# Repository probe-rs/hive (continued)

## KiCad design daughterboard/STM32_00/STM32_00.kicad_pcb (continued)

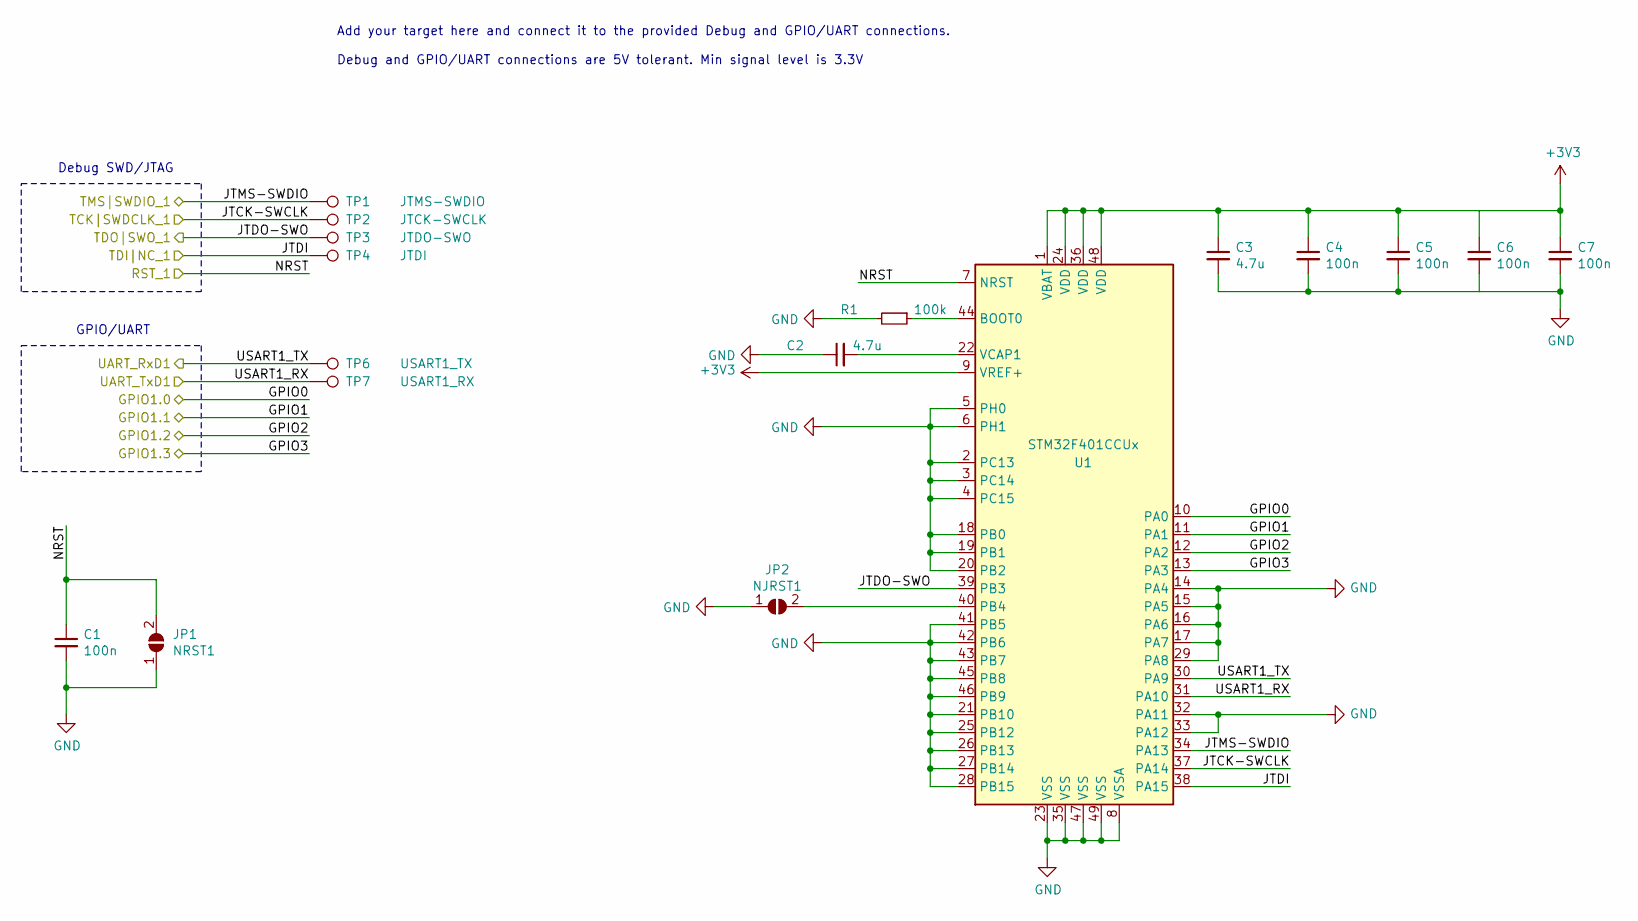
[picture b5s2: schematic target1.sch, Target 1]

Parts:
C1, C4, C5, C6, C7: 100n; C_0603_1608Metric_Pad1.05x0.95mm_HandSolder
C2, C3: 4.7u; C_0603_1608Metric_Pad1.05x0.95mm_HandSolder
JP1: NRST1; SolderJumper-2_P1.3mm_Open_TrianglePad1.0x1.5mm
JP2: NJRST1; SolderJumper-2_P1.3mm_Open_TrianglePad1.0x1.5mm
R1: 100k; R_0603_1608Metric_Pad1.05x0.95mm_HandSolder
TP1: JTMS-SWDIO; TestPoint_Pad_1.0x1.0mm
TP2: JTCK-SWCLK; TestPoint_Pad_1.0x1.0mm
TP3: JTDO-SWO; TestPoint_Pad_1.0x1.0mm
TP4: JTDI; TestPoint_Pad_1.0x1.0mm
TP6: USART1_TX; TestPoint_Pad_1.0x1.0mm
TP7: USART1_RX; TestPoint_Pad_1.0x1.0mm
U1: STM32F401CCUx; QFN-48-1EP_7x7mm_P0.5mm_EP5.6x5.6mm

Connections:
+3V3: C3.1, C4.1, C5.1, C6.1, C7.1, U1.1 (VBAT), U1.9 (VREF+), U1.24 (VDD), U1.36 (VDD), U1.48 (VDD); also elsewhere on the board
/Target 1/GPIO1.0: U1.10 (PA0); also elsewhere on the board
/Target 1/GPIO1.1: U1.11 (PA1); also elsewhere on the board
/Target 1/GPIO1.2: U1.12 (PA2); also elsewhere on the board
/Target 1/GPIO1.3: U1.13 (PA3); also elsewhere on the board
/Target 1/RST_1: C1.1, JP1.2 (B), U1.7 (NRST); also elsewhere on the board
/Target 1/TCK|SWDCLK_1: TP2.1, U1.37 (PA14); also elsewhere on the board
/Target 1/TDI|NC_1: TP4.1, U1.38 (PA15); also elsewhere on the board
/Target 1/TDO|SWO_1: TP3.1, U1.39 (PB3); also elsewhere on the board
/Target 1/TMS|SWDIO_1: TP1.1, U1.34 (PA13); also elsewhere on the board
/Target 1/UART_RxD1: TP6.1, U1.30 (PA9); also elsewhere on the board
/Target 1/UART_TxD1: TP7.1, U1.31 (PA10); also elsewhere on the board
GND: C1.2, C2.1, C3.2, C4.2, C5.2, C6.2, C7.2, JP1.1 (A), JP2.1 (A), R1.2, U1.2 (PC13), U1.3 (PC14), U1.4 (PC15), U1.5 (PH0), U1.6 (PH1), U1.8 (VSSA), U1.14 (PA4), U1.15 (PA5), U1.16 (PA6), U1.17 (PA7), U1.18 (PB0), U1.19 (PB1), U1.20 (PB2), U1.21 (PB10), U1.23 (VSS), U1.25 (PB12), U1.26 (PB13), U1.27 (PB14), U1.28 (PB15), U1.29 (PA8), U1.32 (PA11), U1.33 (PA12), U1.35 (VSS), U1.41 (PB5), U1.42 (PB6), U1.43 (PB7), U1.45 (PB8), U1.46 (PB9), U1.47 (VSS), U1.49 (VSS); also elsewhere on the board
unnamed: C2.2, U1.22 (VCAP1)
unnamed: JP2.2 (B), U1.40 (PB4)
unnamed: R1.1, U1.44 (BOOT0)

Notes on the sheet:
Debug SWD/JTAG
GPIO/UART
Add your target here and connect it to the provided Debug and GPIO/UART connections. Debug and GPIO/UART connections are 5V tolerant. Min signal level is 3.3V

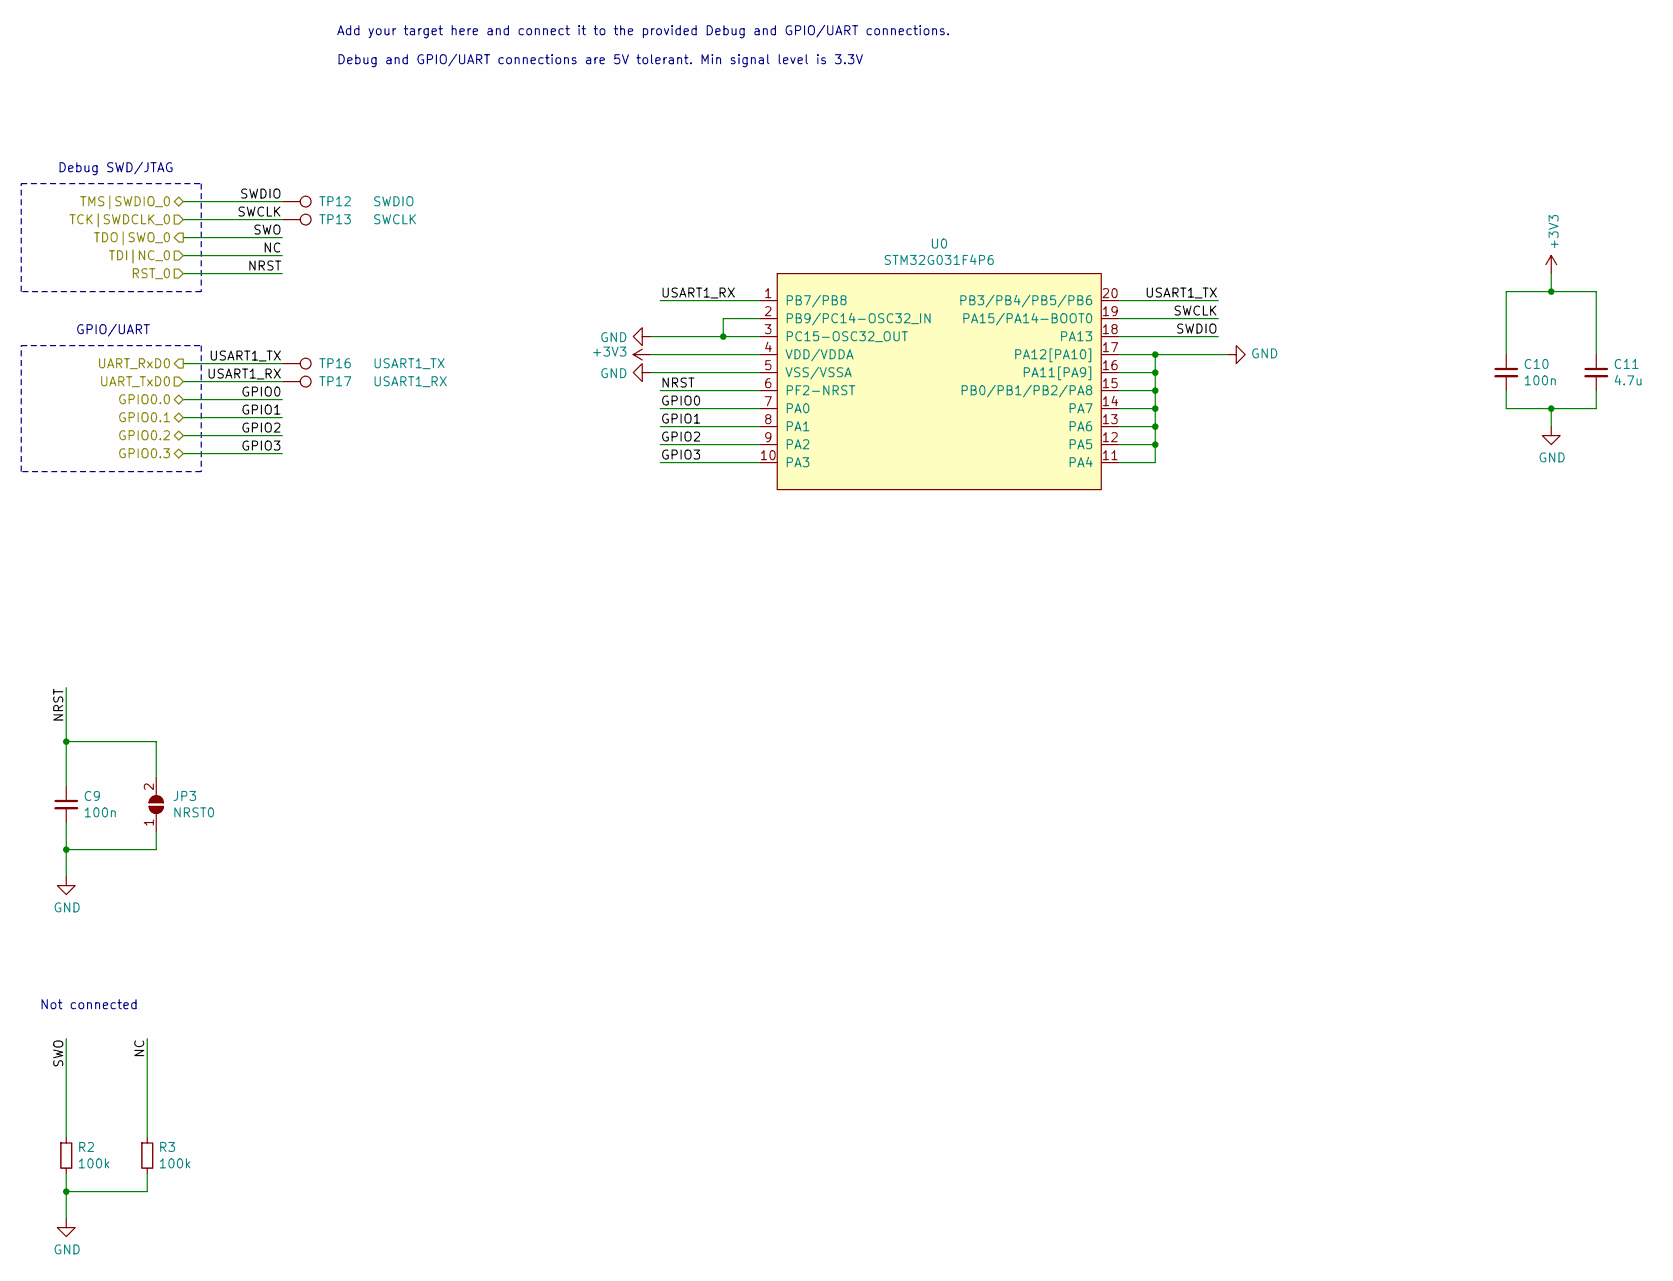
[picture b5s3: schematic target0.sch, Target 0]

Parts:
C9, C10: 100n; C_0603_1608Metric_Pad1.05x0.95mm_HandSolder
C11: 4.7u; C_0603_1608Metric_Pad1.05x0.95mm_HandSolder
JP3: NRST0; SolderJumper-2_P1.3mm_Open_TrianglePad1.0x1.5mm
R2, R3: 100k; R_0603_1608Metric_Pad1.05x0.95mm_HandSolder
TP12: SWDIO; TestPoint_Pad_1.0x1.0mm
TP13: SWCLK; TestPoint_Pad_1.0x1.0mm
TP16: USART1_TX; TestPoint_Pad_1.0x1.0mm
TP17: USART1_RX; TestPoint_Pad_1.0x1.0mm
U0: STM32G031F4P6; SOP65P640X120-20N

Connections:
+3V3: C10.1, C11.1, U0.4 (VDD/VDDA); also elsewhere on the board
/Target 0/GPIO0.0: U0.7 (PA0); also elsewhere on the board
/Target 0/GPIO0.1: U0.8 (PA1); also elsewhere on the board
/Target 0/GPIO0.2: U0.9 (PA2); also elsewhere on the board
/Target 0/GPIO0.3: U0.10 (PA3); also elsewhere on the board
/Target 0/RST_0: C9.1, JP3.2 (B), U0.6 (PF2-NRST); also elsewhere on the board
/Target 0/TCK|SWDCLK_0: TP13.1, U0.19 (PA15/PA14-BOOT0); also elsewhere on the board
/Target 0/TDI|NC_0: R3.1; also elsewhere on the board
/Target 0/TDO|SWO_0: R2.1; also elsewhere on the board
/Target 0/TMS|SWDIO_0: TP12.1, U0.18 (PA13); also elsewhere on the board
/Target 0/UART_RxD0: TP16.1, U0.20 (PB3/PB4/PB5/PB6); also elsewhere on the board
/Target 0/UART_TxD0: TP17.1, U0.1 (PB7/PB8); also elsewhere on the board
GND: C9.2, C10.2, C11.2, JP3.1 (A), R2.2, R3.2, U0.2 (PB9/PC14-OSC32_IN), U0.3 (PC15-OSC32_OUT), U0.5 (VSS/VSSA), U0.11 (PA4), U0.12 (PA5), U0.13 (PA6), U0.14 (PA7), U0.15 (PB0/PB1/PB2/PA8), U0.16 (PA11[PA9]), U0.17 (PA12[PA10]); also elsewhere on the board

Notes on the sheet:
Debug SWD/JTAG
GPIO/UART
Add your target here and connect it to the provided Debug and GPIO/UART connections. Debug and GPIO/UART connections are 5V tolerant. Min signal level is 3.3V
Not connected

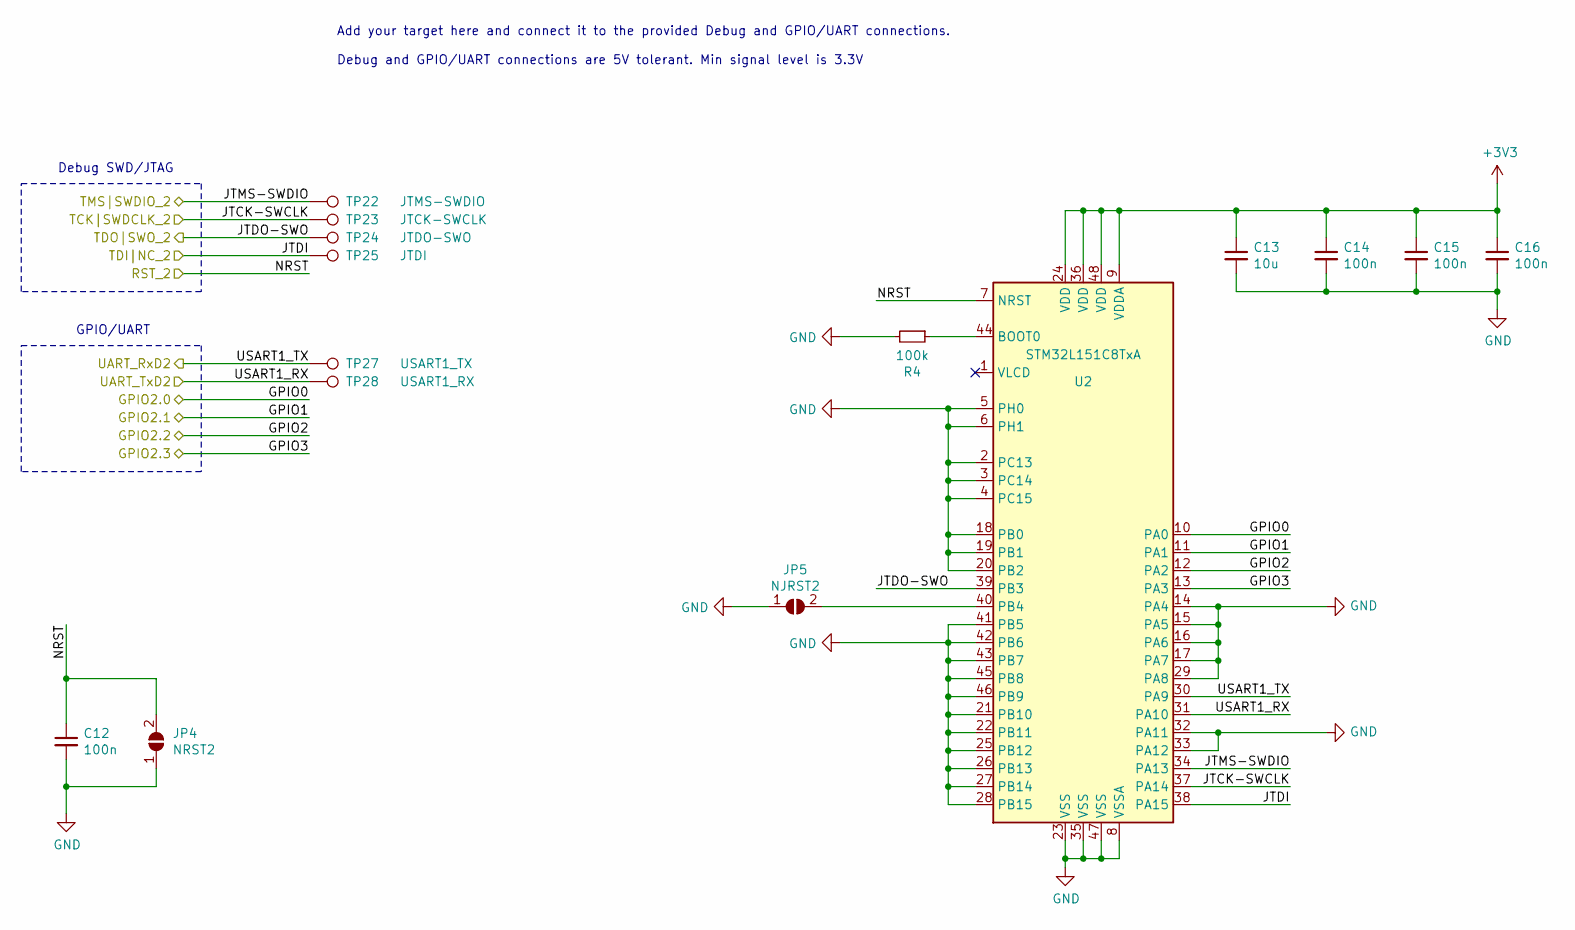
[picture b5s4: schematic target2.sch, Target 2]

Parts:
C12, C14, C15, C16: 100n; C_0603_1608Metric_Pad1.05x0.95mm_HandSolder
C13: 10u; C_0603_1608Metric_Pad1.05x0.95mm_HandSolder
JP4: NRST2; SolderJumper-2_P1.3mm_Open_TrianglePad1.0x1.5mm
JP5: NJRST2; SolderJumper-2_P1.3mm_Open_TrianglePad1.0x1.5mm
R4: 100k; R_0603_1608Metric_Pad1.05x0.95mm_HandSolder
TP22: JTMS-SWDIO; TestPoint_Pad_1.0x1.0mm
TP23: JTCK-SWCLK; TestPoint_Pad_1.0x1.0mm
TP24: JTDO-SWO; TestPoint_Pad_1.0x1.0mm
TP25: JTDI; TestPoint_Pad_1.0x1.0mm
TP27: USART1_TX; TestPoint_Pad_1.0x1.0mm
TP28: USART1_RX; TestPoint_Pad_1.0x1.0mm
U2: STM32L151C8TxA; LQFP-48_7x7mm_P0.5mm

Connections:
+3V3: C13.1, C14.1, C15.1, C16.1, U2.9 (VDDA), U2.24 (VDD), U2.36 (VDD), U2.48 (VDD); also elsewhere on the board
/Target 2/GPIO2.0: U2.10 (PA0); also elsewhere on the board
/Target 2/GPIO2.1: U2.11 (PA1); also elsewhere on the board
/Target 2/GPIO2.2: U2.12 (PA2); also elsewhere on the board
/Target 2/GPIO2.3: U2.13 (PA3); also elsewhere on the board
/Target 2/RST_2: C12.1, JP4.2 (B), U2.7 (NRST); also elsewhere on the board
/Target 2/TCK|SWDCLK_2: TP23.1, U2.37 (PA14); also elsewhere on the board
/Target 2/TDI|NC_2: TP25.1, U2.38 (PA15); also elsewhere on the board
/Target 2/TDO|SWO_2: TP24.1, U2.39 (PB3); also elsewhere on the board
/Target 2/TMS|SWDIO_2: TP22.1, U2.34 (PA13); also elsewhere on the board
/Target 2/UART_RxD2: TP27.1, U2.30 (PA9); also elsewhere on the board
/Target 2/UART_TxD2: TP28.1, U2.31 (PA10); also elsewhere on the board
GND: C12.2, C13.2, C14.2, C15.2, C16.2, JP4.1 (A), JP5.1 (A), R4.2, U2.2 (PC13), U2.3 (PC14), U2.4 (PC15), U2.5 (PH0), U2.6 (PH1), U2.8 (VSSA), U2.14 (PA4), U2.15 (PA5), U2.16 (PA6), U2.17 (PA7), U2.18 (PB0), U2.19 (PB1), U2.20 (PB2), U2.21 (PB10), U2.22 (PB11), U2.23 (VSS), U2.25 (PB12), U2.26 (PB13), U2.27 (PB14), U2.28 (PB15), U2.29 (PA8), U2.32 (PA11), U2.33 (PA12), U2.35 (VSS), U2.41 (PB5), U2.42 (PB6), U2.43 (PB7), U2.45 (PB8), U2.46 (PB9), U2.47 (VSS); also elsewhere on the board
unnamed: JP5.2 (B), U2.40 (PB4)
unnamed: R4.1, U2.44 (BOOT0)

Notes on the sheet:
Debug SWD/JTAG
GPIO/UART
Add your target here and connect it to the provided Debug and GPIO/UART connections. Debug and GPIO/UART connections are 5V tolerant. Min signal level is 3.3V

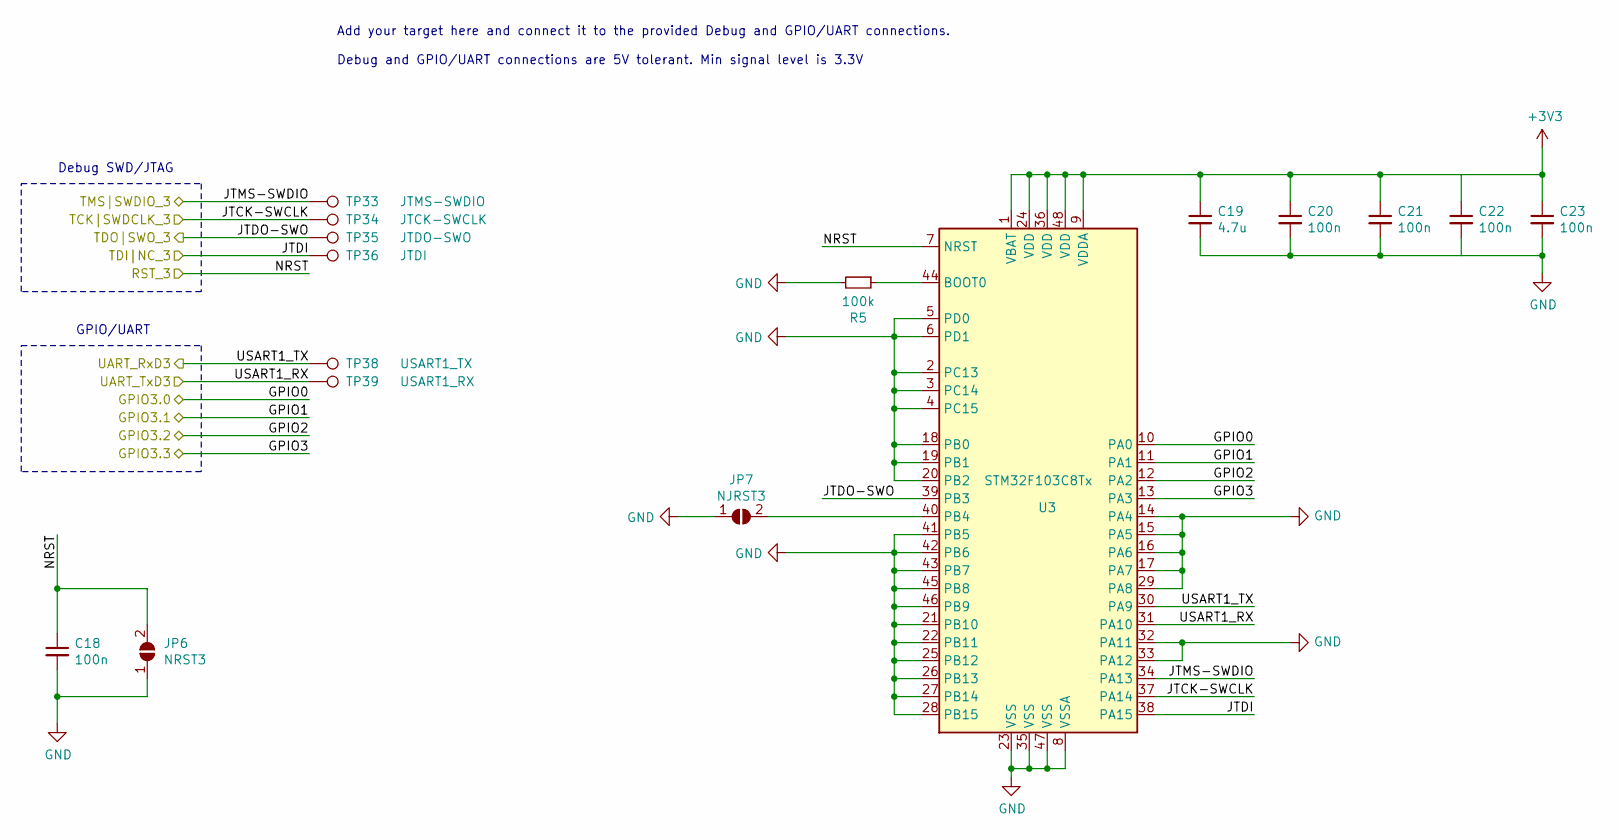
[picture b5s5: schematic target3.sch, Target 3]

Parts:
C18, C20, C21, C22, C23: 100n; C_0603_1608Metric_Pad1.05x0.95mm_HandSolder
C19: 4.7u; C_0603_1608Metric_Pad1.05x0.95mm_HandSolder
JP6: NRST3; SolderJumper-2_P1.3mm_Open_TrianglePad1.0x1.5mm
JP7: NJRST3; SolderJumper-2_P1.3mm_Open_TrianglePad1.0x1.5mm
R5: 100k; R_0603_1608Metric_Pad1.05x0.95mm_HandSolder
TP33: JTMS-SWDIO; TestPoint_Pad_1.0x1.0mm
TP34: JTCK-SWCLK; TestPoint_Pad_1.0x1.0mm
TP35: JTDO-SWO; TestPoint_Pad_1.0x1.0mm
TP36: JTDI; TestPoint_Pad_1.0x1.0mm
TP38: USART1_TX; TestPoint_Pad_1.0x1.0mm
TP39: USART1_RX; TestPoint_Pad_1.0x1.0mm
U3: STM32F103C8Tx; LQFP-48_7x7mm_P0.5mm

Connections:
+3V3: C19.1, C20.1, C21.1, C22.1, C23.1, U3.1 (VBAT), U3.9 (VDDA), U3.24 (VDD), U3.36 (VDD), U3.48 (VDD); also elsewhere on the board
/Target 3/GPIO3.0: U3.10 (PA0); also elsewhere on the board
/Target 3/GPIO3.1: U3.11 (PA1); also elsewhere on the board
/Target 3/GPIO3.2: U3.12 (PA2); also elsewhere on the board
/Target 3/GPIO3.3: U3.13 (PA3); also elsewhere on the board
/Target 3/RST_3: C18.1, JP6.2 (B), U3.7 (NRST); also elsewhere on the board
/Target 3/TCK|SWDCLK_3: TP34.1, U3.37 (PA14); also elsewhere on the board
/Target 3/TDI|NC_3: TP36.1, U3.38 (PA15); also elsewhere on the board
/Target 3/TDO|SWO_3: TP35.1, U3.39 (PB3); also elsewhere on the board
/Target 3/TMS|SWDIO_3: TP33.1, U3.34 (PA13); also elsewhere on the board
/Target 3/UART_RxD3: TP38.1, U3.30 (PA9); also elsewhere on the board
/Target 3/UART_TxD3: TP39.1, U3.31 (PA10); also elsewhere on the board
GND: C18.2, C19.2, C20.2, C21.2, C22.2, C23.2, JP6.1 (A), JP7.1 (A), R5.2, U3.2 (PC13), U3.3 (PC14), U3.4 (PC15), U3.5 (PD0), U3.6 (PD1), U3.8 (VSSA), U3.14 (PA4), U3.15 (PA5), U3.16 (PA6), U3.17 (PA7), U3.18 (PB0), U3.19 (PB1), U3.20 (PB2), U3.21 (PB10), U3.22 (PB11), U3.23 (VSS), U3.25 (PB12), U3.26 (PB13), U3.27 (PB14), U3.28 (PB15), U3.29 (PA8), U3.32 (PA11), U3.33 (PA12), U3.35 (VSS), U3.41 (PB5), U3.42 (PB6), U3.43 (PB7), U3.45 (PB8), U3.46 (PB9), U3.47 (VSS); also elsewhere on the board
unnamed: JP7.2 (B), U3.40 (PB4)
unnamed: R5.1, U3.44 (BOOT0)

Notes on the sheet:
Debug SWD/JTAG
GPIO/UART
Add your target here and connect it to the provided Debug and GPIO/UART connections. Debug and GPIO/UART connections are 5V tolerant. Min signal level is 3.3V

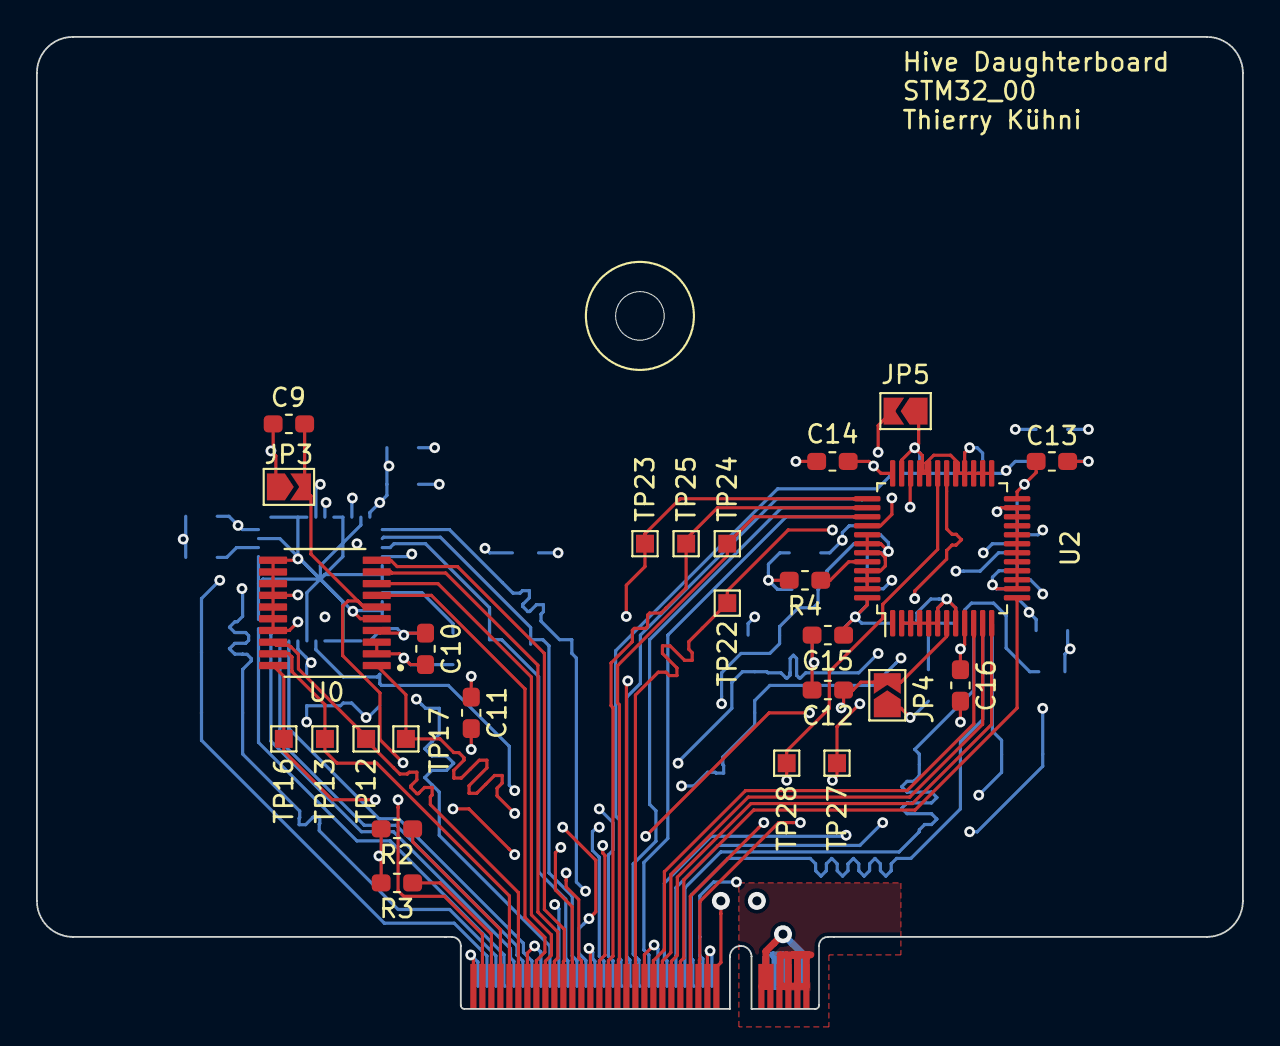
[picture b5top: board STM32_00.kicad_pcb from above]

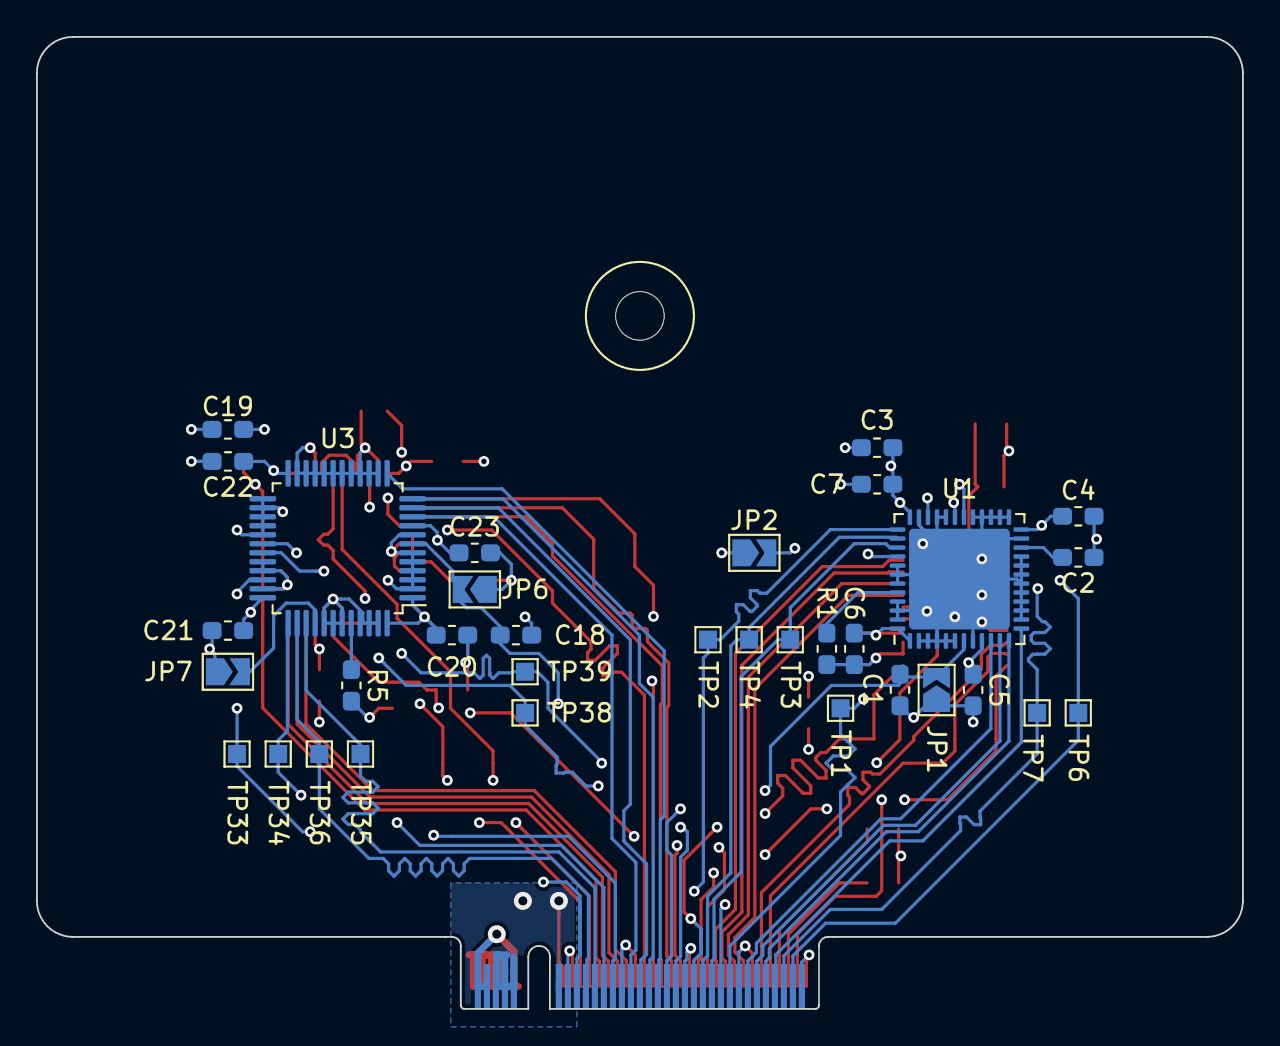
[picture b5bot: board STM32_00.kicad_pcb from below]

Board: 4 copper layers, 67.0 x 54.0 mm, 61 parts (33 on the bottom side), 54 nets.

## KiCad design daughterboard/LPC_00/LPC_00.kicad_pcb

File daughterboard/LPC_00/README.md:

## Daughterboard LPC_00
This Daughterboard features several LPC MCUs.

### Targets
The following targets are implemented on this Daughterboard:
| Designation | MCU |
| --- | --- |
| target0 | LPC845M301JHI33Y |
| target1 | LPC1114FDH28/102:5 |
| target2 | LPC55S69JBD64K |
| target3 | LPC1313FBD48/01,15 |

### Partlist
The partlist for this Daughterboard is available [here](https://octopart.com/bom-tool/fNupy8w4).

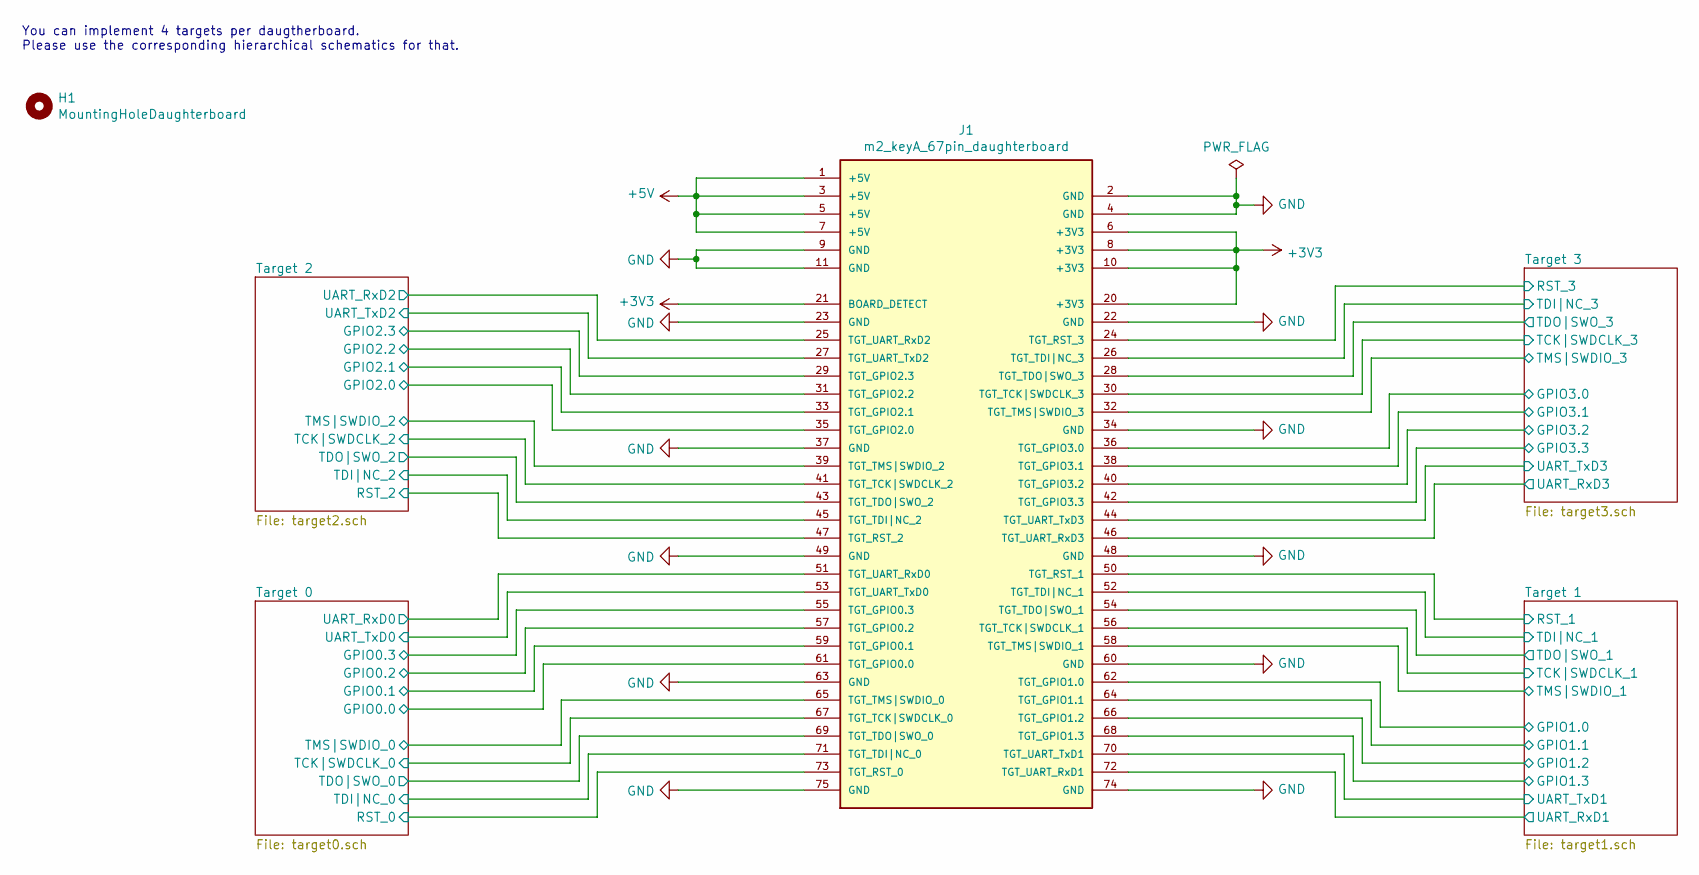
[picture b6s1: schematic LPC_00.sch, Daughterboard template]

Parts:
H1: MountingHoleDaughterboard; MountingHole_2.7mm_M2.5
J1: m2_keyA_67pin_daughterboard; m2_keyB

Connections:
+3V3: J1.6 (+3V3), J1.8 (+3V3), J1.10 (+3V3), J1.20 (+3V3), J1.21 (BOARD_DETECT); also elsewhere on the board
+5V: J1.1 (+5V), J1.3 (+5V), J1.5 (+5V), J1.7 (+5V)
/Target 0/GPIO0.0: J1.61 (TGT_GPIO0.0); also elsewhere on the board
/Target 0/GPIO0.1: J1.59 (TGT_GPIO0.1); also elsewhere on the board
/Target 0/GPIO0.2: J1.57 (TGT_GPIO0.2); also elsewhere on the board
/Target 0/GPIO0.3: J1.55 (TGT_GPIO0.3); also elsewhere on the board
/Target 0/RST_0: J1.73 (TGT_RST_0); also elsewhere on the board
/Target 0/TCK|SWDCLK_0: J1.67 (TGT_TCK|SWDCLK_0); also elsewhere on the board
/Target 0/TDI|NC_0: J1.71 (TGT_TDI|NC_0); also elsewhere on the board
/Target 0/TDO|SWO_0: J1.69 (TGT_TDO|SWO_0); also elsewhere on the board
/Target 0/TMS|SWDIO_0: J1.65 (TGT_TMS|SWDIO_0); also elsewhere on the board
/Target 0/UART_RxD0: J1.51 (TGT_UART_RxD0); also elsewhere on the board
/Target 0/UART_TxD0: J1.53 (TGT_UART_TxD0); also elsewhere on the board
/Target 1/GPIO1.0: J1.62 (TGT_GPIO1.0); also elsewhere on the board
/Target 1/GPIO1.1: J1.64 (TGT_GPIO1.1); also elsewhere on the board
/Target 1/GPIO1.2: J1.66 (TGT_GPIO1.2); also elsewhere on the board
/Target 1/GPIO1.3: J1.68 (TGT_GPIO1.3); also elsewhere on the board
/Target 1/RST_1: J1.50 (TGT_RST_1); also elsewhere on the board
/Target 1/TCK|SWDCLK_1: J1.56 (TGT_TCK|SWDCLK_1); also elsewhere on the board
/Target 1/TDI|NC_1: J1.52 (TGT_TDI|NC_1); also elsewhere on the board
/Target 1/TDO|SWO_1: J1.54 (TGT_TDO|SWO_1); also elsewhere on the board
/Target 1/TMS|SWDIO_1: J1.58 (TGT_TMS|SWDIO_1); also elsewhere on the board
/Target 1/UART_RxD1: J1.72 (TGT_UART_RxD1); also elsewhere on the board
/Target 1/UART_TxD1: J1.70 (TGT_UART_TxD1); also elsewhere on the board
/Target 2/GPIO2.0: J1.35 (TGT_GPIO2.0); also elsewhere on the board
/Target 2/GPIO2.1: J1.33 (TGT_GPIO2.1); also elsewhere on the board
/Target 2/GPIO2.2: J1.31 (TGT_GPIO2.2); also elsewhere on the board
/Target 2/GPIO2.3: J1.29 (TGT_GPIO2.3); also elsewhere on the board
/Target 2/RST_2: J1.47 (TGT_RST_2); also elsewhere on the board
/Target 2/TCK|SWDCLK_2: J1.41 (TGT_TCK|SWDCLK_2); also elsewhere on the board
/Target 2/TDI|NC_2: J1.45 (TGT_TDI|NC_2); also elsewhere on the board
/Target 2/TDO|SWO_2: J1.43 (TGT_TDO|SWO_2); also elsewhere on the board
/Target 2/TMS|SWDIO_2: J1.39 (TGT_TMS|SWDIO_2); also elsewhere on the board
/Target 2/UART_RxD2: J1.25 (TGT_UART_RxD2); also elsewhere on the board
/Target 2/UART_TxD2: J1.27 (TGT_UART_TxD2); also elsewhere on the board
/Target 3/GPIO3.0: J1.36 (TGT_GPIO3.0); also elsewhere on the board
/Target 3/GPIO3.1: J1.38 (TGT_GPIO3.1); also elsewhere on the board
/Target 3/GPIO3.2: J1.40 (TGT_GPIO3.2); also elsewhere on the board
/Target 3/GPIO3.3: J1.42 (TGT_GPIO3.3); also elsewhere on the board
/Target 3/RST_3: J1.24 (TGT_RST_3); also elsewhere on the board
/Target 3/TCK|SWDCLK_3: J1.30 (TGT_TCK|SWDCLK_3); also elsewhere on the board
/Target 3/TDI|NC_3: J1.26 (TGT_TDI|NC_3); also elsewhere on the board
/Target 3/TDO|SWO_3: J1.28 (TGT_TDO|SWO_3); also elsewhere on the board
/Target 3/TMS|SWDIO_3: J1.32 (TGT_TMS|SWDIO_3); also elsewhere on the board
/Target 3/UART_RxD3: J1.46 (TGT_UART_RxD3); also elsewhere on the board
/Target 3/UART_TxD3: J1.44 (TGT_UART_TxD3); also elsewhere on the board
GND: J1.2 (GND), J1.4 (GND), J1.9 (GND), J1.11 (GND), J1.22 (GND), J1.23 (GND), J1.34 (GND), J1.37 (GND), J1.48 (GND), J1.49 (GND), J1.60 (GND), J1.63 (GND), J1.74 (GND), J1.75 (GND); also elsewhere on the board

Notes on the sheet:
You can implement 4 targets per daugtherboard. Please use the corresponding hierarchical schematics for that.

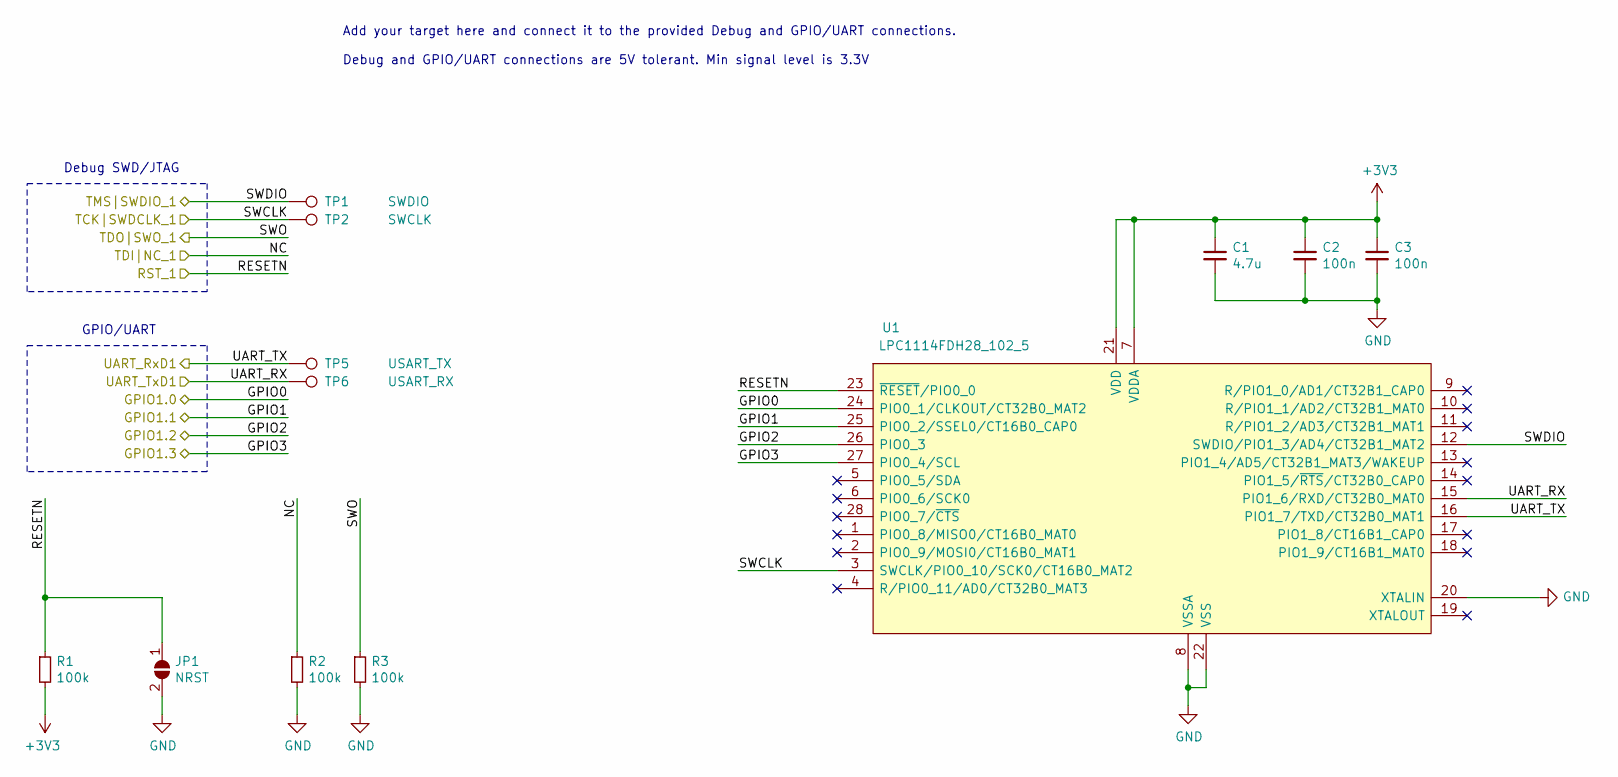
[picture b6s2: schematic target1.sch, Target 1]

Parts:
C1: 4.7u; C_0603_1608Metric_Pad1.05x0.95mm_HandSolder
C2, C3: 100n; C_0603_1608Metric_Pad1.05x0.95mm_HandSolder
JP1: NRST; SolderJumper-2_P1.3mm_Open_TrianglePad1.0x1.5mm
R1, R2, R3: 100k; R_0603_1608Metric_Pad1.05x0.95mm_HandSolder
TP1: SWDIO; TestPoint_Pad_1.0x1.0mm
TP2: SWCLK; TestPoint_Pad_1.0x1.0mm
TP5: USART_TX; TestPoint_Pad_1.0x1.0mm
TP6: USART_RX; TestPoint_Pad_1.0x1.0mm
U1: LPC1114FDH28_102_5; LPC1114FDH28_1025; Mouser Part Number 771-LPC1114FDH28/102

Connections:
+3V3: C1.1, C2.1, C3.1, R1.2, U1.7 (VDDA), U1.21 (VDD); also elsewhere on the board
/Target 1/GPIO1.0: U1.24 (PIO0_1/CLKOUT/CT32B0_MAT2); also elsewhere on the board
/Target 1/GPIO1.1: U1.25 (PIO0_2/SSEL0/CT16B0_CAP0); also elsewhere on the board
/Target 1/GPIO1.2: U1.26 (PIO0_3); also elsewhere on the board
/Target 1/GPIO1.3: U1.27 (PIO0_4/SCL); also elsewhere on the board
/Target 1/RST_1: JP1.1 (A), R1.1, U1.23 (~RESET~/PIO0_0); also elsewhere on the board
/Target 1/TCK|SWDCLK_1: TP2.1, U1.3 (SWCLK/PIO0_10/SCK0/CT16B0_MAT2); also elsewhere on the board
/Target 1/TDI|NC_1: R2.1; also elsewhere on the board
/Target 1/TDO|SWO_1: R3.1; also elsewhere on the board
/Target 1/TMS|SWDIO_1: TP1.1, U1.12 (SWDIO/PIO1_3/AD4/CT32B1_MAT2); also elsewhere on the board
/Target 1/UART_RxD1: TP5.1, U1.16 (PIO1_7/TXD/CT32B0_MAT1); also elsewhere on the board
/Target 1/UART_TxD1: TP6.1, U1.15 (PIO1_6/RXD/CT32B0_MAT0); also elsewhere on the board
GND: C1.2, C2.2, C3.2, JP1.2 (B), R2.2, R3.2, U1.8 (VSSA), U1.20 (XTALIN), U1.22 (VSS); also elsewhere on the board

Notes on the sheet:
Debug SWD/JTAG
GPIO/UART
Add your target here and connect it to the provided Debug and GPIO/UART connections. Debug and GPIO/UART connections are 5V tolerant. Min signal level is 3.3V

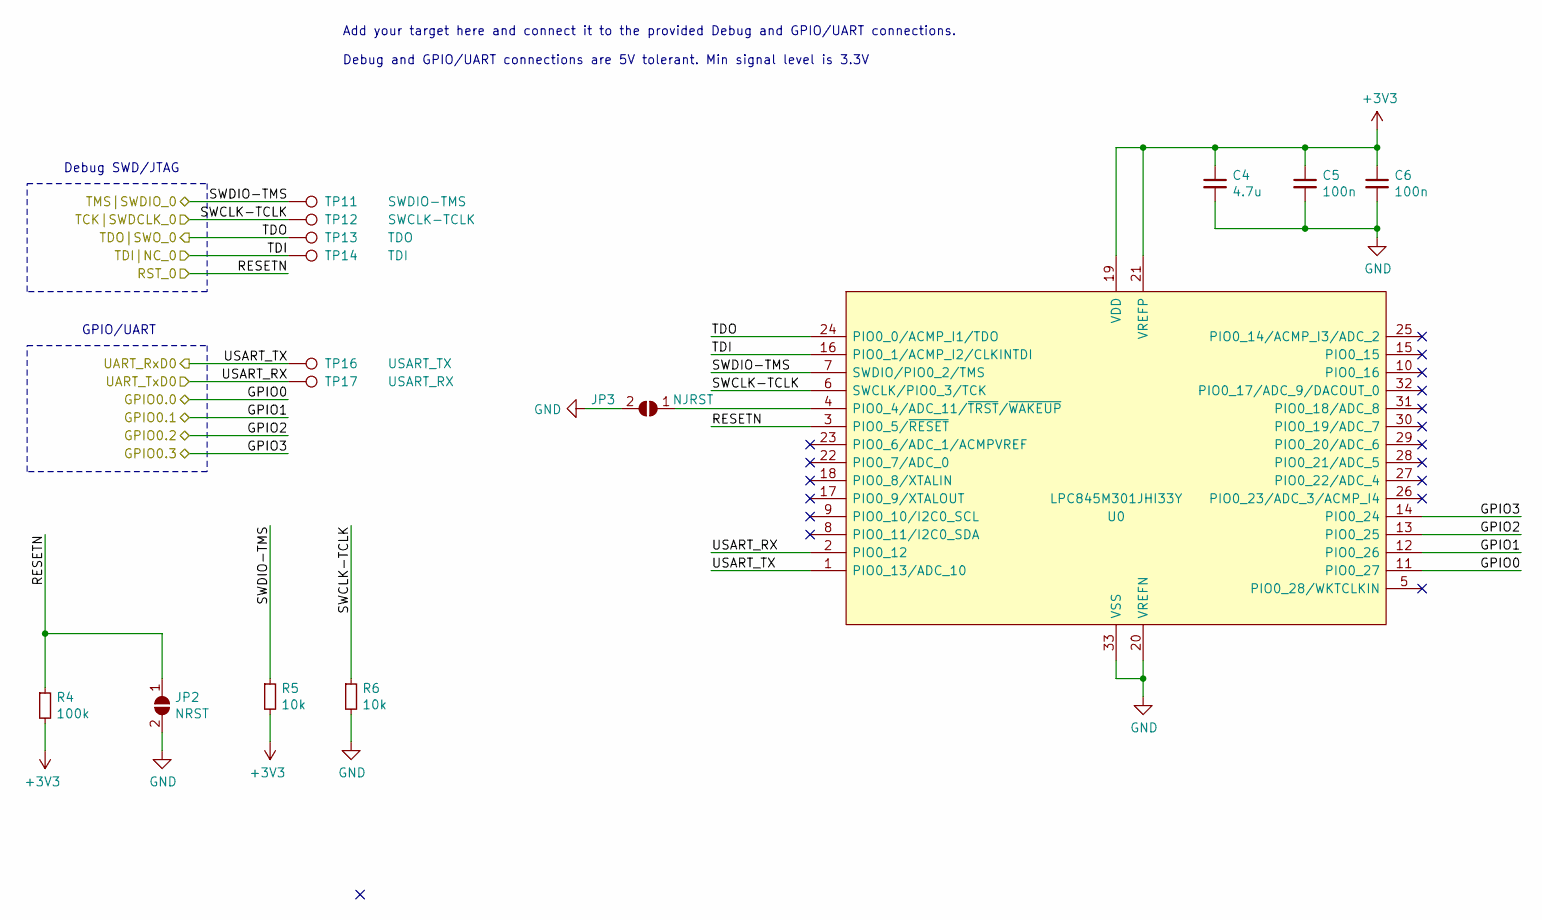
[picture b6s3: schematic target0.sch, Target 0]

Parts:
C4: 4.7u; C_0603_1608Metric_Pad1.05x0.95mm_HandSolder
C5, C6: 100n; C_0603_1608Metric_Pad1.05x0.95mm_HandSolder
JP2: NRST; SolderJumper-2_P1.3mm_Open_TrianglePad1.0x1.5mm
JP3: NJRST; SolderJumper-2_P1.3mm_Open_TrianglePad1.0x1.5mm
R4: 100k; R_0603_1608Metric_Pad1.05x0.95mm_HandSolder
R5, R6: 10k; R_0603_1608Metric_Pad1.05x0.95mm_HandSolder
TP11: SWDIO-TMS; TestPoint_Pad_1.0x1.0mm
TP12: SWCLK-TCLK; TestPoint_Pad_1.0x1.0mm
TP13: TDO; TestPoint_Pad_1.0x1.0mm
TP14: TDI; TestPoint_Pad_1.0x1.0mm
TP16: USART_TX; TestPoint_Pad_1.0x1.0mm
TP17: USART_RX; TestPoint_Pad_1.0x1.0mm
U0: LPC845M301JHI33Y; Mouser Part Number 771-LPC845M301JHI33Y

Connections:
+3V3: C4.1, C5.1, C6.1, R4.2, R5.2, U0.19 (VDD), U0.21 (VREFP); also elsewhere on the board
/Target 0/GPIO0.0: U0.11 (PIO0_27); also elsewhere on the board
/Target 0/GPIO0.1: U0.12 (PIO0_26); also elsewhere on the board
/Target 0/GPIO0.2: U0.13 (PIO0_25); also elsewhere on the board
/Target 0/GPIO0.3: U0.14 (PIO0_24); also elsewhere on the board
/Target 0/RST_0: JP2.1 (A), R4.1, U0.3 (PIO0_5/~RESET); also elsewhere on the board
/Target 0/TCK|SWDCLK_0: R6.1, TP12.1, U0.6 (SWCLK/PIO0_3/TCK); also elsewhere on the board
/Target 0/TDI|NC_0: TP14.1, U0.16 (PIO0_1/ACMP_I2/CLKINTDI); also elsewhere on the board
/Target 0/TDO|SWO_0: TP13.1, U0.24 (PIO0_0/ACMP_I1/TDO); also elsewhere on the board
/Target 0/TMS|SWDIO_0: R5.1, TP11.1, U0.7 (SWDIO/PIO0_2/TMS); also elsewhere on the board
/Target 0/UART_RxD0: TP16.1, U0.1 (PIO0_13/ADC_10); also elsewhere on the board
/Target 0/UART_TxD0: TP17.1, U0.2 (PIO0_12); also elsewhere on the board
GND: C4.2, C5.2, C6.2, JP2.2 (B), JP3.2 (B), R6.2, U0.20 (VREFN), U0.33 (VSS); also elsewhere on the board
unnamed: JP3.1 (A), U0.4 (PIO0_4/ADC_11/~TRST~/~WAKEUP)

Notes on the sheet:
Debug SWD/JTAG
GPIO/UART
Add your target here and connect it to the provided Debug and GPIO/UART connections. Debug and GPIO/UART connections are 5V tolerant. Min signal level is 3.3V
